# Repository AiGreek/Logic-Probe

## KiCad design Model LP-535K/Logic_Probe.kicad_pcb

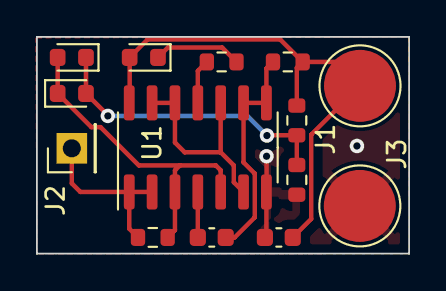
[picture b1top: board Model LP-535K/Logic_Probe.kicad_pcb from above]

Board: 2 copper layers, 20.7 x 12.0 mm, 14 parts (0 on the bottom side), 10 nets.

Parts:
C1, C2: 0.1uF; C_0603_1608Metric
D1: HIGH; LED_0603_1608Metric
D2: LOW; LED_0603_1608Metric
D3: CLK; LED_0603_1608Metric
J1, J3: Conn_01x01; TestPoint_Pad_D4.0mm
J2: Conn_01x01; PinHeader_1x01_P2.54mm_Vertical
R1: 2.2M; R_0603_1608Metric
R2: 1.5K; R_0603_1608Metric
R3, R5: 1.8K; R_0603_1608Metric
R4: 6.8M; R_0603_1608Metric
U1: 4001; SOIC-14_3.9x8.7mm_P1.27mm

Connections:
GND: C1.2, J3.1, R3.2, U1.7 (VSS)
unnamed: C2.2, R4.2, U1.8, U1.9
unnamed: D1.2 (A), D2.1 (K), R1.2, U1.3, U1.5
unnamed: D1.1 (K), D2.2 (A), R2.1, R3.1
unnamed: D3.1 (K), R5.1
unnamed: R5.2, U1.11
unnamed: J2.1, R1.1, U1.1, U1.2
unnamed: C2.1, U1.4
unnamed: U1.6, U1.10, U1.12, U1.13
VCC: C1.1, D3.2 (A), J1.1, R2.2, R4.1, U1.14 (VDD)

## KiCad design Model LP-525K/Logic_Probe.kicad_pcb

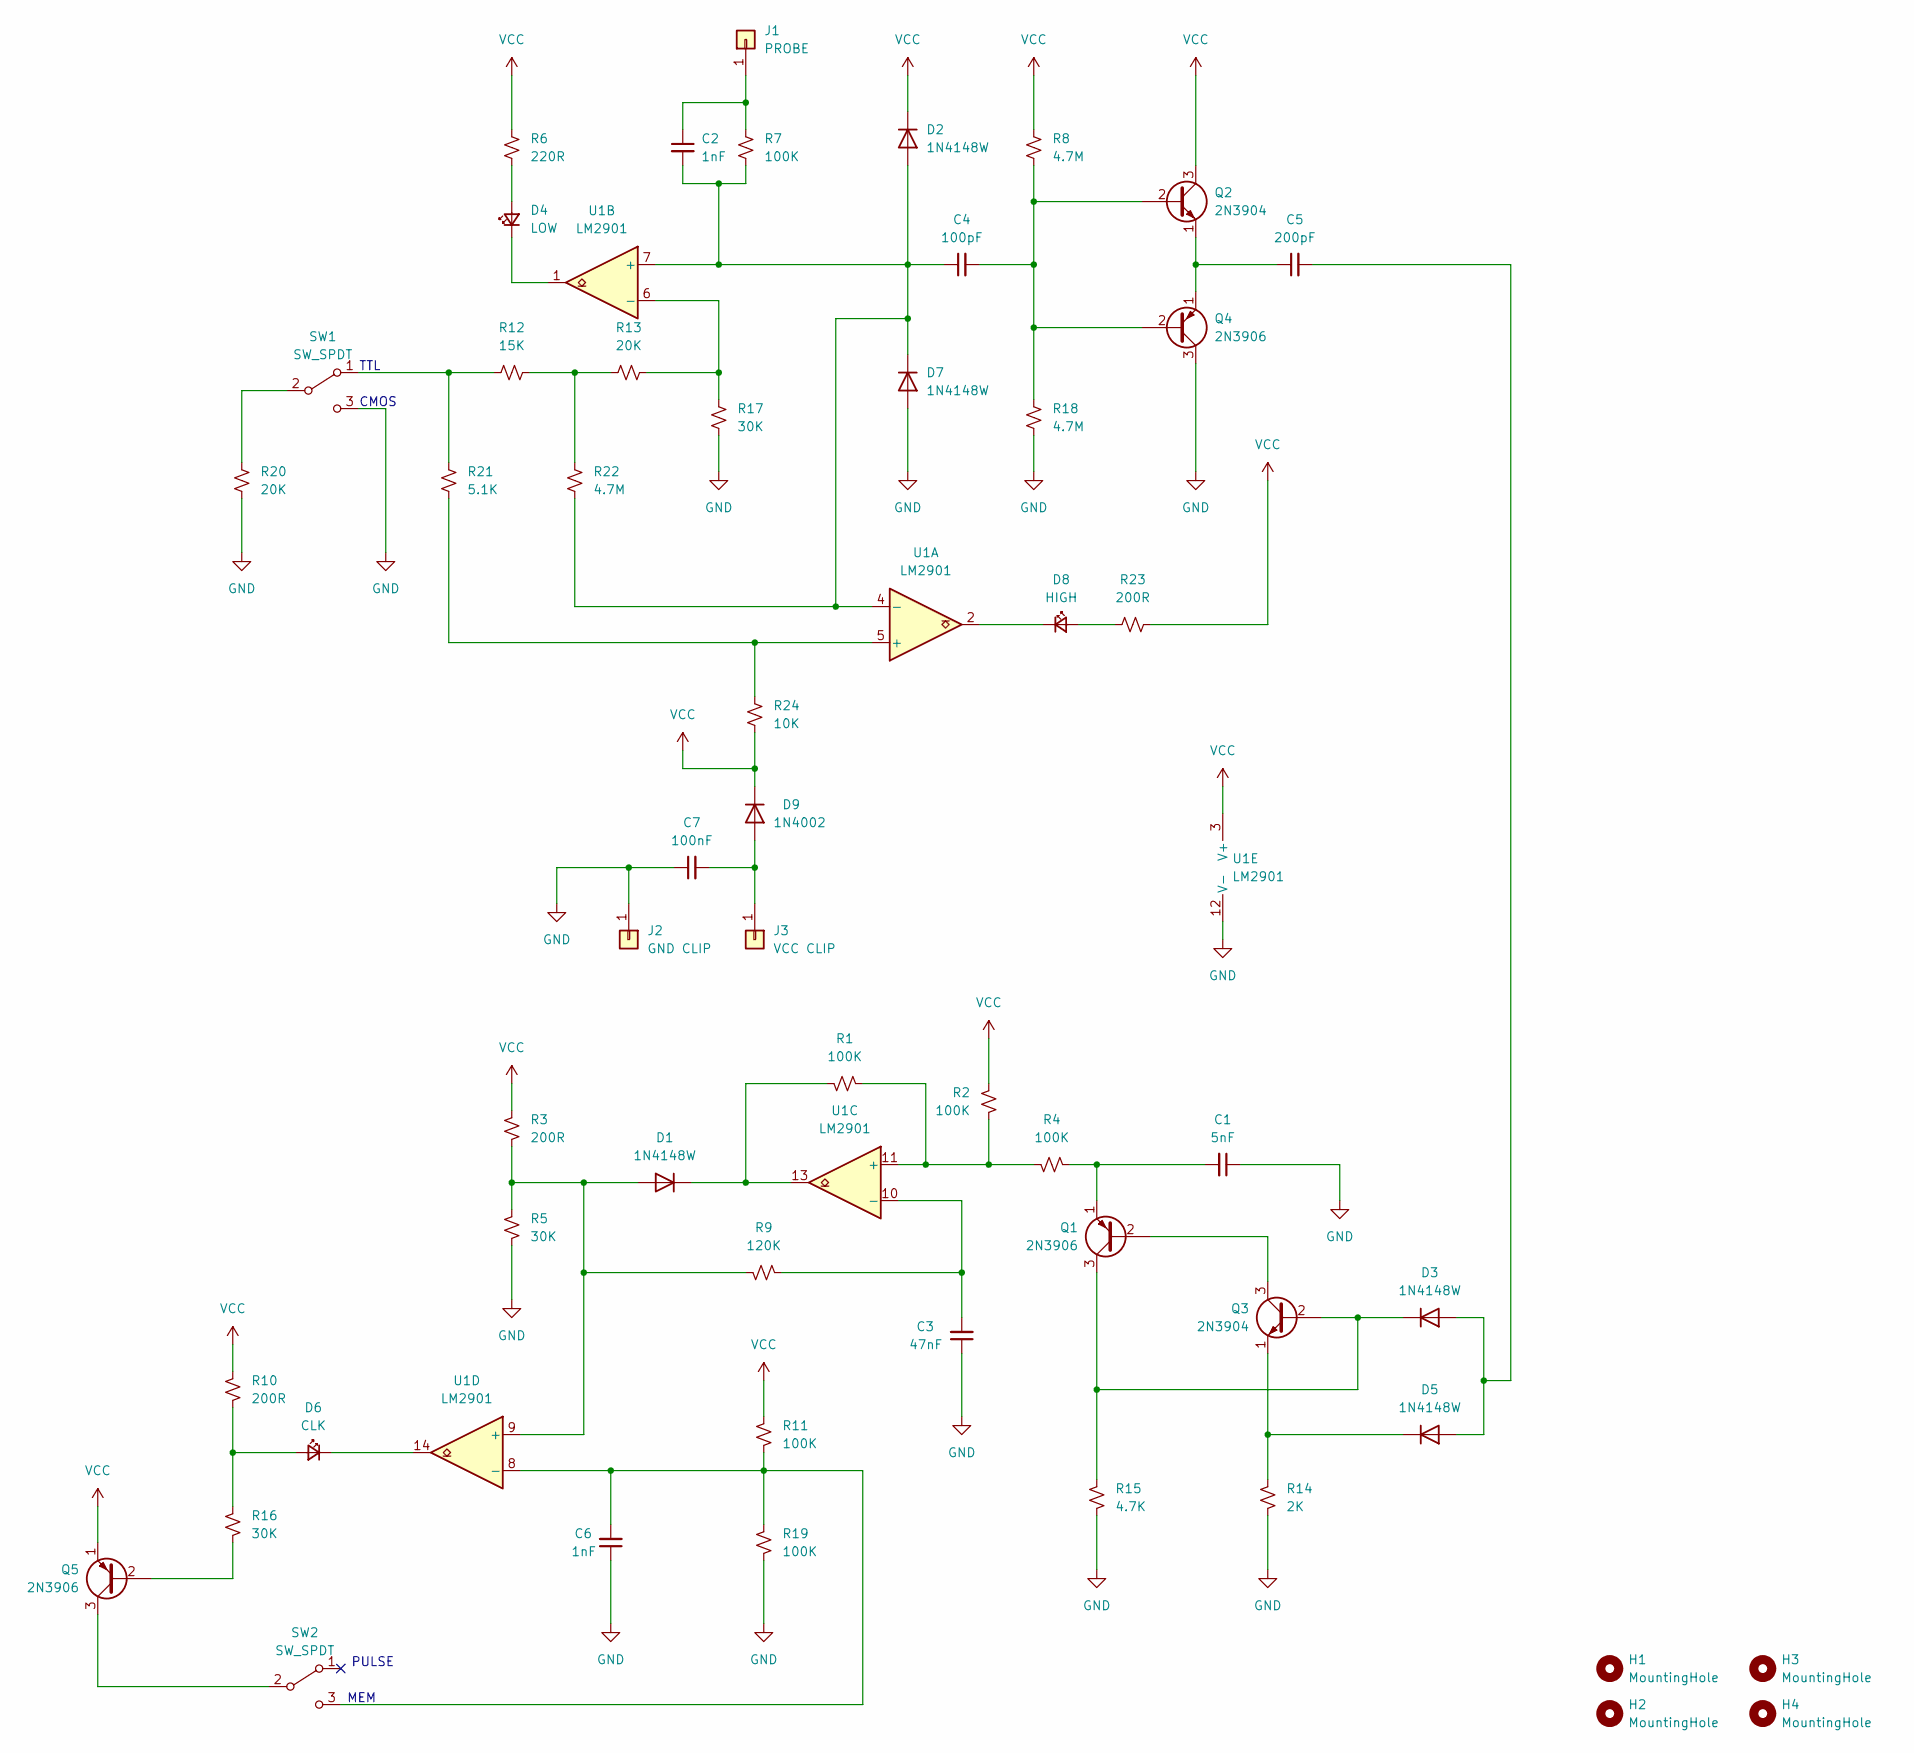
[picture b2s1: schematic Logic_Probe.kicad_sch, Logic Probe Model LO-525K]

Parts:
C1: 5nF; C_0805_2012Metric
C2, C6: 1nF; C_0805_2012Metric
C3: 47nF; C_0805_2012Metric
C4: 100pF; C_0805_2012Metric
C5: 200pF; C_0805_2012Metric
C7: 100nF; C_0805_2012Metric
D1, D2, D3, D5, D7: 1N4148W; D_SOD-123
D4: LOW; LED_D3.0mm_FlatTop
D6: CLK; LED_D3.0mm_FlatTop
D8: HIGH; LED_D3.0mm_FlatTop
D9: 1N4002; D_SOD-123
H1, H2, H3, H4: MountingHole; MountingHole_2.2mm_M2_DIN965
J1: PROBE; Banana_Jack_1Pin
J2: GND CLIP; Banana_Jack_1Pin
J3: VCC CLIP; Banana_Jack_1Pin
Q1, Q4, Q5: 2N3906; TO-92_Inline
Q2, Q3: 2N3904; TO-92_Inline
R1, R2, R4, R7, R11, R19: 100K; R_0805_2012Metric
R3, R10, R23: 200R; R_0805_2012Metric
R5, R16, R17: 30K; R_0805_2012Metric
R6: 220R; R_0805_2012Metric
R8, R18, R22: 4.7M; R_0805_2012Metric
R9: 120K; R_0805_2012Metric
R12: 15K; R_0805_2012Metric
R13, R20: 20K; R_0805_2012Metric
R14: 2K; R_0805_2012Metric
R15: 4.7K; R_0805_2012Metric
R21: 5.1K; R_0805_2012Metric
R24: 10K; R_0805_2012Metric
SW1, SW2: SW_SPDT; SW_Slide_1P2T_CK_OS102011MS2Q
U1: LM2901; SOIC-14_3.9x8.7mm_P1.27mm

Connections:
GND: C1.1, C3.1, C6.1, C7.1, D7.2 (A), J2.1, Q4.3 (C), R5.2, R14.2, R15.2, R17.2, R18.2, R19.2, R20.1, SW1.3 (C), U1.12 (V-)
unnamed: D1.2 (A), R3.2, R5.1, R9.1, U1.9 (+)
unnamed: D1.1 (K), R1.1, U1.13
unnamed: C2.2, C4.1, D2.2 (A), D7.1 (K), R7.2, R22.1, U1.4 (-), U1.7 (+)
unnamed: C5.2, D3.2 (A), D5.2 (A)
unnamed: D3.1 (K), Q1.3 (C), Q3.2 (B), R15.1
unnamed: D4.2 (A), R6.2
unnamed: D4.1 (K), U1.1
unnamed: D5.1 (K), Q3.1 (E), R14.1
unnamed: D6.2 (A), R10.2, R16.1
unnamed: D6.1 (K), U1.14
unnamed: D8.2 (A), R23.1
unnamed: D8.1 (K), U1.2
unnamed: C7.2, D9.2 (A), J3.1
unnamed: C2.1, J1.1, R7.1
unnamed: Q1.2 (B), Q3.3 (C)
unnamed: C1.2, Q1.1 (E), R4.1
unnamed: C4.2, Q2.2 (B), Q4.2 (B), R8.2, R18.1
unnamed: C5.1, Q2.1 (E), Q4.1 (E)
unnamed: Q5.2 (B), R16.2
unnamed: Q5.3 (C), SW2.2 (B)
unnamed: R12.2, R13.1, R22.2
unnamed: R12.1, R21.2, SW1.1 (A)
unnamed: R20.2, SW1.2 (B)
unnamed: C6.2, R11.2, R19.1, SW2.3 (C), U1.8 (-)
unnamed: R21.1, R24.1, U1.5 (+)
unnamed: R13.2, R17.1, U1.6 (-)
unnamed: R1.2, R2.1, R4.2, U1.11 (+)
unnamed: C3.2, R9.2, U1.10 (-)
VCC: D2.1 (K), D9.1 (K), Q2.3 (C), Q5.1 (E), R2.2, R3.1, R6.1, R8.1, R10.1, R11.1, R23.2, R24.2, U1.3 (V+)

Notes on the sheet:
CMOS
MEM
PULSE
TTL

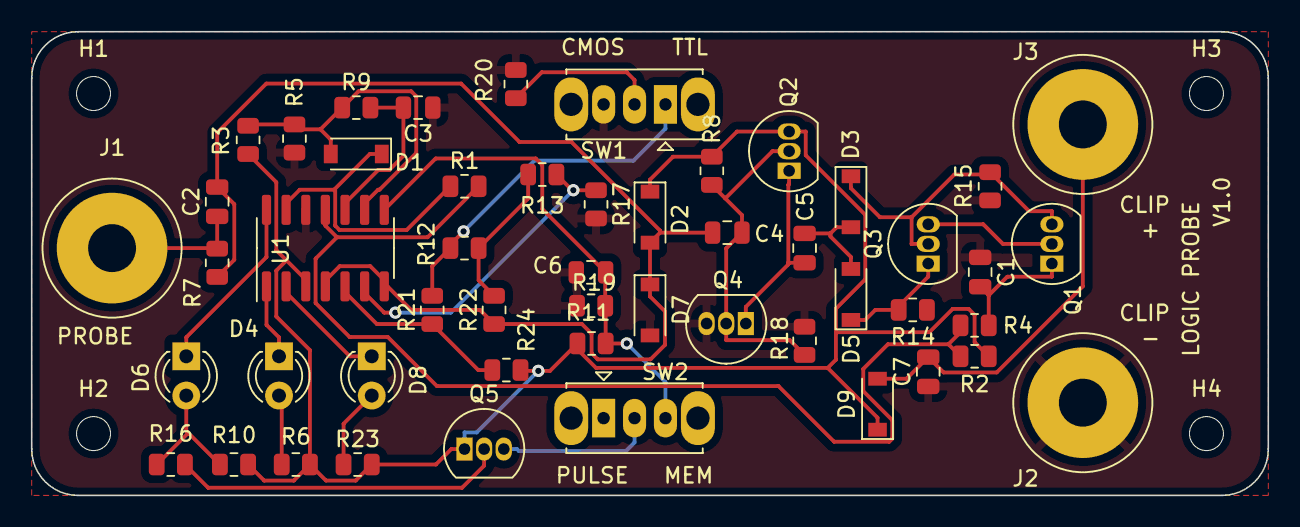
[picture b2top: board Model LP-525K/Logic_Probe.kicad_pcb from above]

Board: 2 copper layers, 80.0 x 30.0 mm, 55 parts (0 on the bottom side), 30 nets.

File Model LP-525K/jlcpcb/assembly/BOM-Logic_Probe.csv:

Comment,Designator,Footprint,LCSC
LM2901,U1,SOIC-14_3.9x8.7mm_P1.27mm,C7932
MountingHole,H4,MountingHole_2.2mm_M2_DIN965,
MountingHole,H3,MountingHole_2.2mm_M2_DIN965,
MountingHole,H2,MountingHole_2.2mm_M2_DIN965,
MountingHole,H1,MountingHole_2.2mm_M2_DIN965,
VCC CLIP,J3,Banana_Jack_1Pin,
1N4148W,D1,D_SOD-123,
100K,R19,R_0805_2012Metric,
200R,R10,R_0805_2012Metric,
2N3906,Q5,TO-92_Inline,
C_Small,C5,C_0805_2012Metric,
1N4148W,D5,D_SOD-123,
100K,R7,R_0805_2012Metric,
2N3906,Q1,TO-92_Inline,
C_Small,C6,C_0805_2012Metric,
10K,R24,R_0805_2012Metric,
30K,R17,R_0805_2012Metric,
4.7M,R18,R_0805_2012Metric,
4.7M,R8,R_0805_2012Metric,
20K,R20,R_0805_2012Metric,
C_Small,C7,C_0805_2012Metric,
SW_SPDT,SW2,SW_Slide_1P2T_CK_OS102011MS2Q,
PROBE,J1,Banana_Jack_1Pin,
100pF,C4,C_0805_2012Metric,
C_Small,C1,C_0805_2012Metric,
100K,R2,R_0805_2012Metric,
100K,R4,R_0805_2012Metric,
4.7M,R22,R_0805_2012Metric,
100K,R11,R_0805_2012Metric,
2N3906,Q4,TO-92_Inline,
200R,R3,R_0805_2012Metric,
SW_SPDT,SW1,SW_Slide_1P2T_CK_OS102011MS2Q,
120K,R9,R_0805_2012Metric,
GND CLIP,J2,Banana_Jack_1Pin,
CLK,D6,LED_D3.0mm_FlatTop,
20K,R13,R_0805_2012Metric,
15K,R12,R_0805_2012Metric,
2N3904,Q2,TO-92_Inline,
100K,R1,R_0805_2012Metric,
HIGH,D8,LED_D3.0mm_FlatTop,
2N3904,Q3,TO-92_Inline,
2K,R14,R_0805_2012Metric,
220R,R6,R_0805_2012Metric,
4.7K,R15,R_0805_2012Metric,
200R,R23,R_0805_2012Metric,
1N4148W,D7,D_SOD-123,
1N4148W,D3,D_SOD-123,
1N4148W,D2,D_SOD-123,
30K,R16,R_0805_2012Metric,
1N4002,D9,D_SOD-123,
LOW,D4,LED_D3.0mm_FlatTop,
C_Small,C3,C_0805_2012Metric,
30K,R5,R_0805_2012Metric,
C_Small,C2,C_0805_2012Metric,
5.1K,R21,R_0805_2012Metric,
